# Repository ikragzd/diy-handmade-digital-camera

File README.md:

# DIY Handmade Digital Camera Prototype

A simple hobby digital camera prototype combining basic embedded camera hardware with a handcrafted, non-plastic exterior enclosure.

## Build Overview
* **Enclosure Materials:** Hand-shaped wooden body finished with acrylic paint and wrapped in waterproof fabric panels.
* **Project Scope:** A personal hardware and craft experiment exploring custom tactile enclosures for compact portable electronics.

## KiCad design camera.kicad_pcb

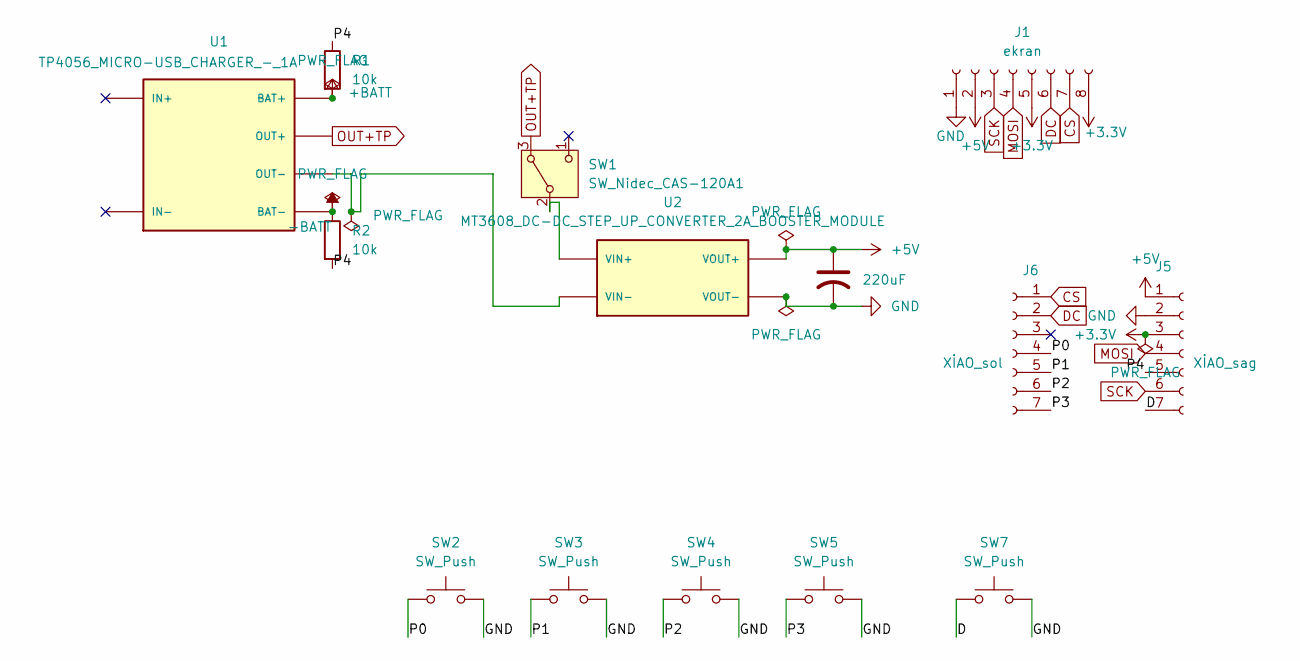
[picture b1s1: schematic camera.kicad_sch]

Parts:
C1: 220uF; CP_Radial_D8.0mm_P3.50mm
J1: ekran; PinSocket_1x08_P2.54mm_Vertical
J5: XİAO_sag; PinSocket_1x07_P2.54mm_Vertical
J6: XİAO_sol; PinSocket_1x07_P2.54mm_Vertical
R1, R2: 10k; R_Axial_DIN0204_L3.6mm_D1.6mm_P1.90mm_Vertical
SW1: SW_Nidec_CAS-120A1; Nidec_Copal_CAS-120A
SW2, SW3, SW4, SW5, SW7: SW_Push; SW_PUSH_6mm
U1: TP4056_MICRO-USB_CHARGER_-_1A; MODULE_TP4056_MICRO-USB_CHARGER_-_1A
U2: MT3608_DC-DC_STEP_UP_CONVERTER_2A_BOOSTER_MODULE; MODULE_MT3608_DC-DC_STEP_UP_CONVERTER_2A_BOOSTER_MODULE

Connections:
+3.3V: J1.5, J1.8, J5.3
+5V: C1.1, J1.2, J5.1, U2.VOUT_P (VOUT+)
+BATT: R1.2, U1.BAT_P (BAT+)
-BATT: R2.1, U1.BAT_N (BAT-)
/D: J5.7, SW7.1
/P0: J6.4, SW2.1
/P1: J6.5, SW3.1
/P2: J6.6, SW4.1
/P3: J6.7, SW5.1
/P4: J5.5, R1.1, R2.2
CS: J1.7, J6.1
DC: J1.6, J6.2
GND: C1.2, J1.1, J5.2, SW2.2, SW3.2, SW4.2, SW5.2, SW7.2, U2.VOUT_N (VOUT-)
MOSI: J1.4, J5.4
unnamed: SW1.2 (B), U2.VIN_P (VIN+)
unnamed: U1.OUT_N (OUT-), U2.VIN_N (VIN-)
OUT+TP: SW1.3 (A), U1.OUT_P (OUT+)
SCK: J1.3, J5.6

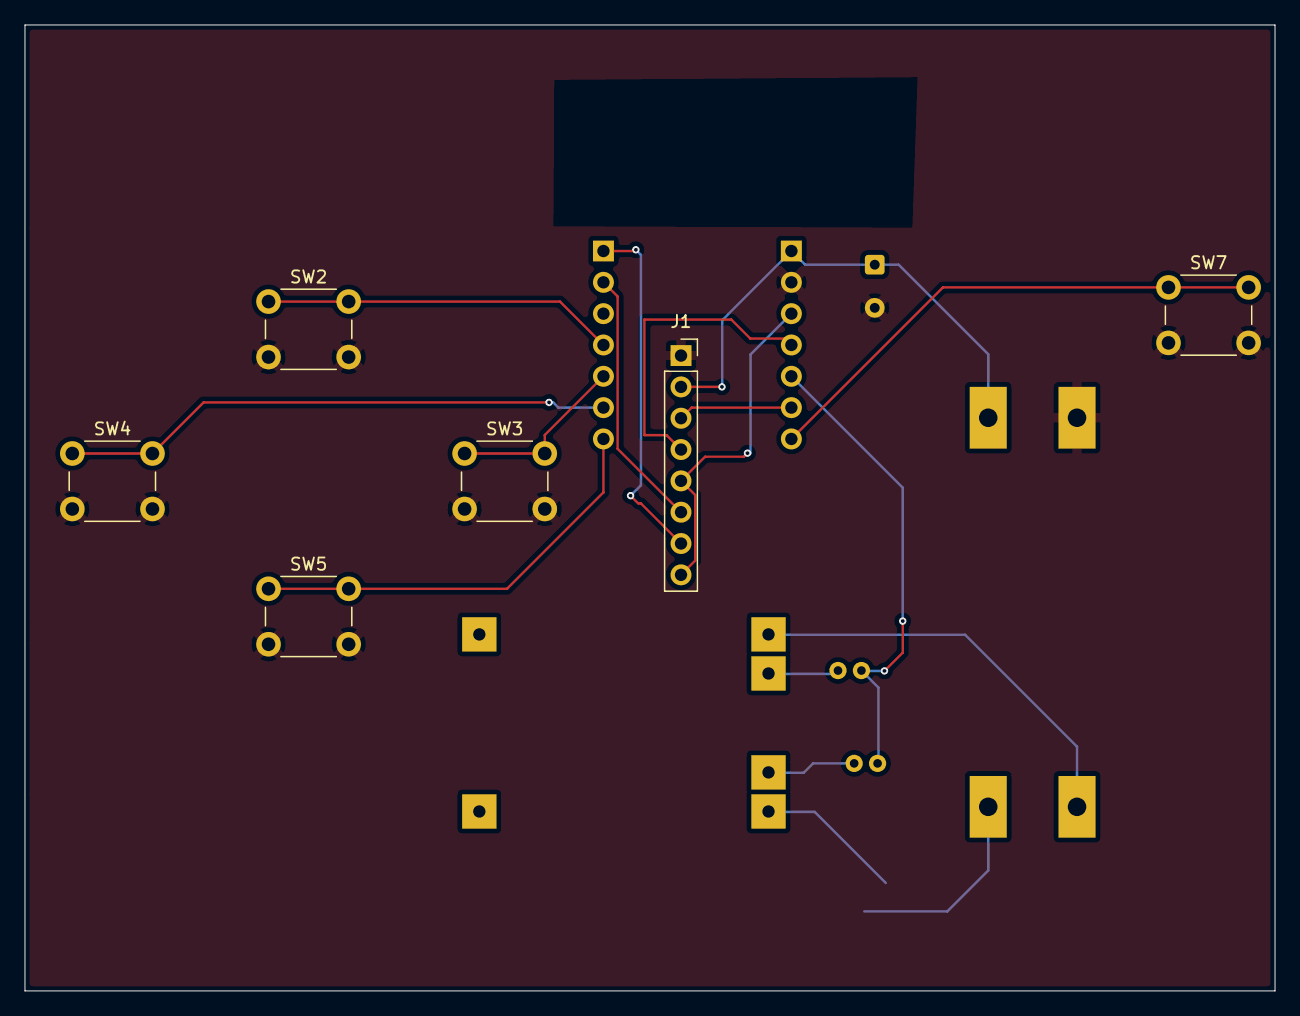
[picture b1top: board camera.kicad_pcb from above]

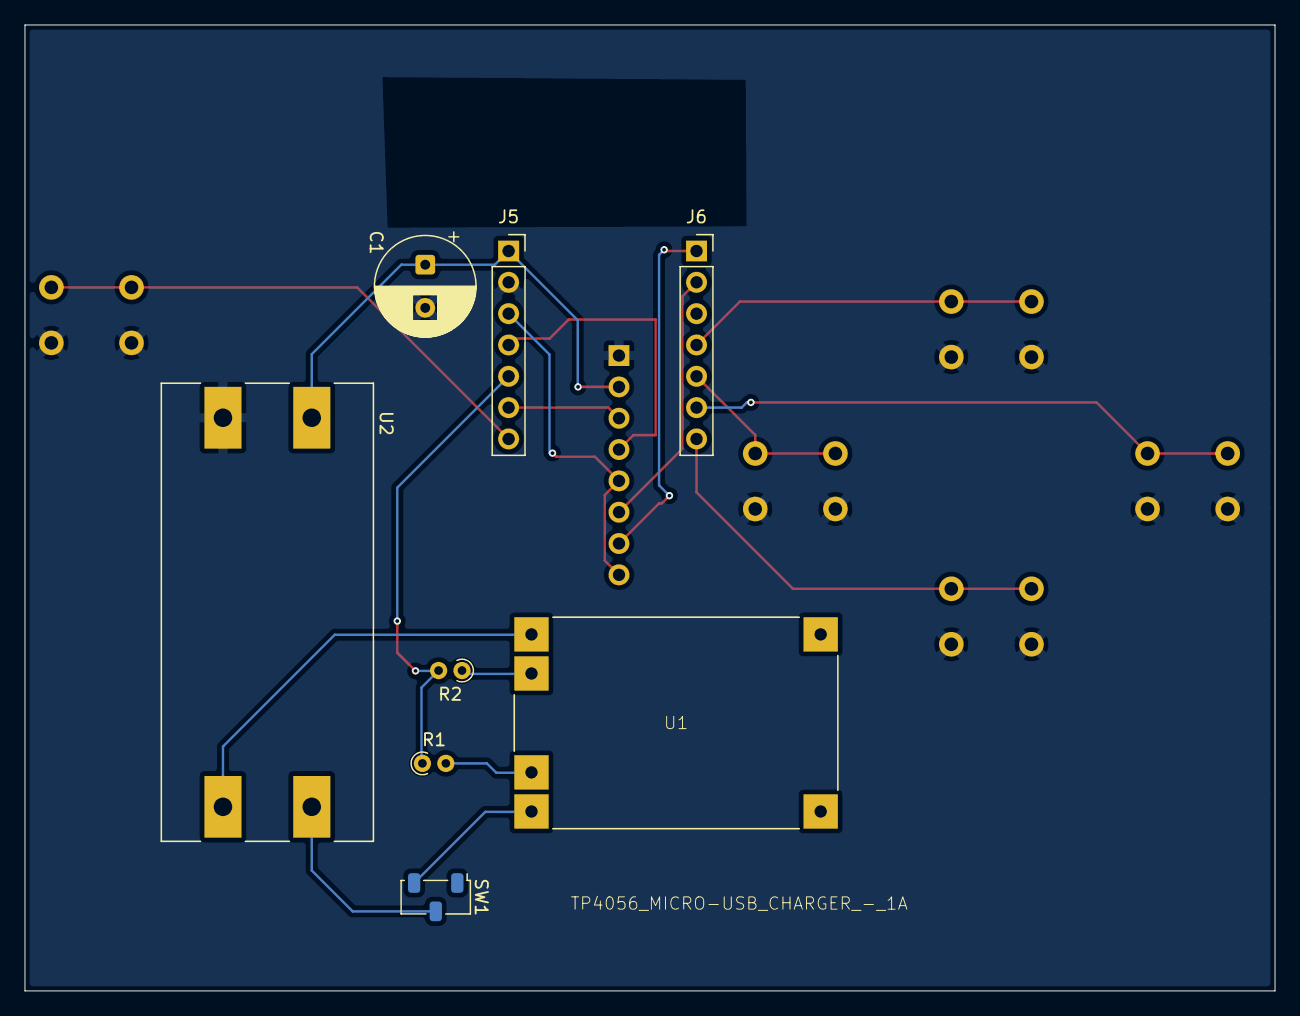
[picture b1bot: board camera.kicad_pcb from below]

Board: 2 copper layers, 101.4 x 78.3 mm, 14 parts (8 on the bottom side), 18 nets.
